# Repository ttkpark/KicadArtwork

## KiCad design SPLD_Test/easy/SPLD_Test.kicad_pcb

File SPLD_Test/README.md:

# CPLD-STM32 UI Controller & FND Multiplexer

## 📌 프로젝트 개요
본 프로젝트는 Altera MAX 3000A(EPM3064) CPLD를 활용하여 메인 MCU(STM32F030)의 부하를 줄이기 위한 하드웨어 UI 컨트롤러를 구현한 설계입니다.  
버튼 입력의 디바운싱(Debouncing), 0~31 양방향 카운터, 그리고 4-Digit 7-Segment(FND)의 다이나믹 구동(Multiplexing)을 CPLD 하드웨어 로직으로 분리 처리합니다.

## 🛠️ 개발 환경 및 하드웨어 사양
- **Target Device:** Altera MAX 3000A 계열 (`EPM3064ALC44-10`)
- **Main MCU:** STM32F030
- **IDE:** Quartus II 13.0 SP1 Web Edition
- **Clock Source:** STM32에서 공급하는 8kHz 외부 클럭 (`IO33`)

## 🎯 주요 기능 (Core Features)
1. **하드웨어 디바운싱 (Debouncing)**  
   - 8kHz 클럭 기반으로 약 18.7ms 딜레이 필터 구현  
   - 버튼 채터링을 소프트웨어 개입 없이 하드웨어에서 차단

2. **5-bit 양방향 카운터 (0~31)**  
   - `BTN1` 입력 시 -1 감소 (0에서 31 순환)  
   - `BTN2`, `BTN4` 입력 시 +1 증가 (31에서 0 순환)

3. **경량화된 BCD 변환 로직**  
   - EPM3064 매크로셀(64) 한계를 고려해 나눗셈/Double Dabble 대신  
   - `if-else` 기반 최적화된 뺄셈 로직으로 10의 자리/1의 자리 분리

4. **FND 다이나믹 멀티플렉싱**  
   - 8kHz를 32분주하여 약 250Hz로 4자리 Common Anode 순차 구동

5. **실시간 MCU 상태 보고**  
   - 카운터 5비트 상태(0~31)를 전용 I/O 핀 5개로 STM32에 비동기 전달

## 🔌 핀맵 할당 (Pin Mapping)
| 기능 그룹 | 신호명 | CPLD 핀 번호 | 비고 |
| :--- | :--- | :--- | :--- |
| **Clock** | `clk_8khz` | 33 | STM32에서 공급받는 8kHz 클럭 |
| **Button Input** | `btn1` | 1 | -1 감소 (Active Low) |
|  | `btn2` | 2 | +1 증가 (Active Low) |
|  | `btn4` | 4 | +1 증가 (Active Low) |
| **MCU Output** | `mcu_28` ~ `mcu_37` | 28, 29, 31, 34, 37 | 카운터 5비트 상태 실시간 출력 |
| **FND Segment** | `seg_a` ~ `dp` | 5, 6, 8, 9, 11, 12, 14, 16 | 7-Segment 제어 (Active Low) |
| **FND Common** | `com1` ~ `com4` | 18, 19, 20, 21 | 자릿수 제어 (Active High) |

> ⚠️ **주의 (하드웨어 핀맵 제약사항)**  
> 3번 핀은 VCC와 물리적으로 결선되어 있어 버튼 입력으로 사용하지 않습니다.

## 🚨 트러블슈팅 및 개발 가이드 (Lessons Learned)
프로젝트 수정/업로드 시 아래 항목을 반드시 확인하세요.

### 1) 98% 프로그래밍 실패(Verification Failed)
- **원인:** Verify 단계에서 JTAG 핀(TDI, TMS 등)에 연결된 외부 소자(FND 등)가 노이즈를 유발
- **해결책:**
  - 프로그래밍 시 **FND 모듈을 일시적으로 탈거**한 상태에서 업로드
  - 임시 조치로 Programmer에서 `Verify` 체크 해제 후 다운로드

### 2) 미사용 핀 설정 (Unused Pins Configuration)
- **원인:** Quartus 기본값이 미사용 핀을 `As output driving ground`로 설정해 전원 충돌 가능
- **해결책:**
  - `Assignments -> Device -> Device and Pin Options -> Unused Pins`
  - 값을 **`As input tri-stated`** 로 변경 후 전체 컴파일

### 3) 디바이스 라이브러리 지원
- MAX 3000A는 최신 Quartus Prime에서 미지원
- **Quartus II 13.0 SP1 Web Edition** 사용
- Device Installer에서 `MAX 3000A` 디바이스 팩(`.qdz`) 추가 설치 필요

## 📁 저장소 구조(예시)
```text
SPLD_Test/
├─ CPLD/          # Quartus 프로젝트/소스
├─ firmware/      # STM32F030 펌웨어 (OLED 모니터)
└─ README.md      # 본 문서
```

## 🔗 관련 문서
- 펌웨어 배선/핀 설명: `firmware/docs/CONNECTIONS.md`
- 펌웨어 개발 문서: `firmware/docs/DEVELOPMENT.md`

## 🙌 회고
하드웨어 핀맵 충돌, JTAG 간섭, 매크로셀 용량 최적화를 모두 통과해 완성한 프로젝트입니다.  
임베디드 하드웨어/펌웨어 협업 개발의 실제 제약과 해법이 담긴 결과물로, 유지보수 시 본 README와 관련 문서를 함께 참고하는 것을 권장합니다.

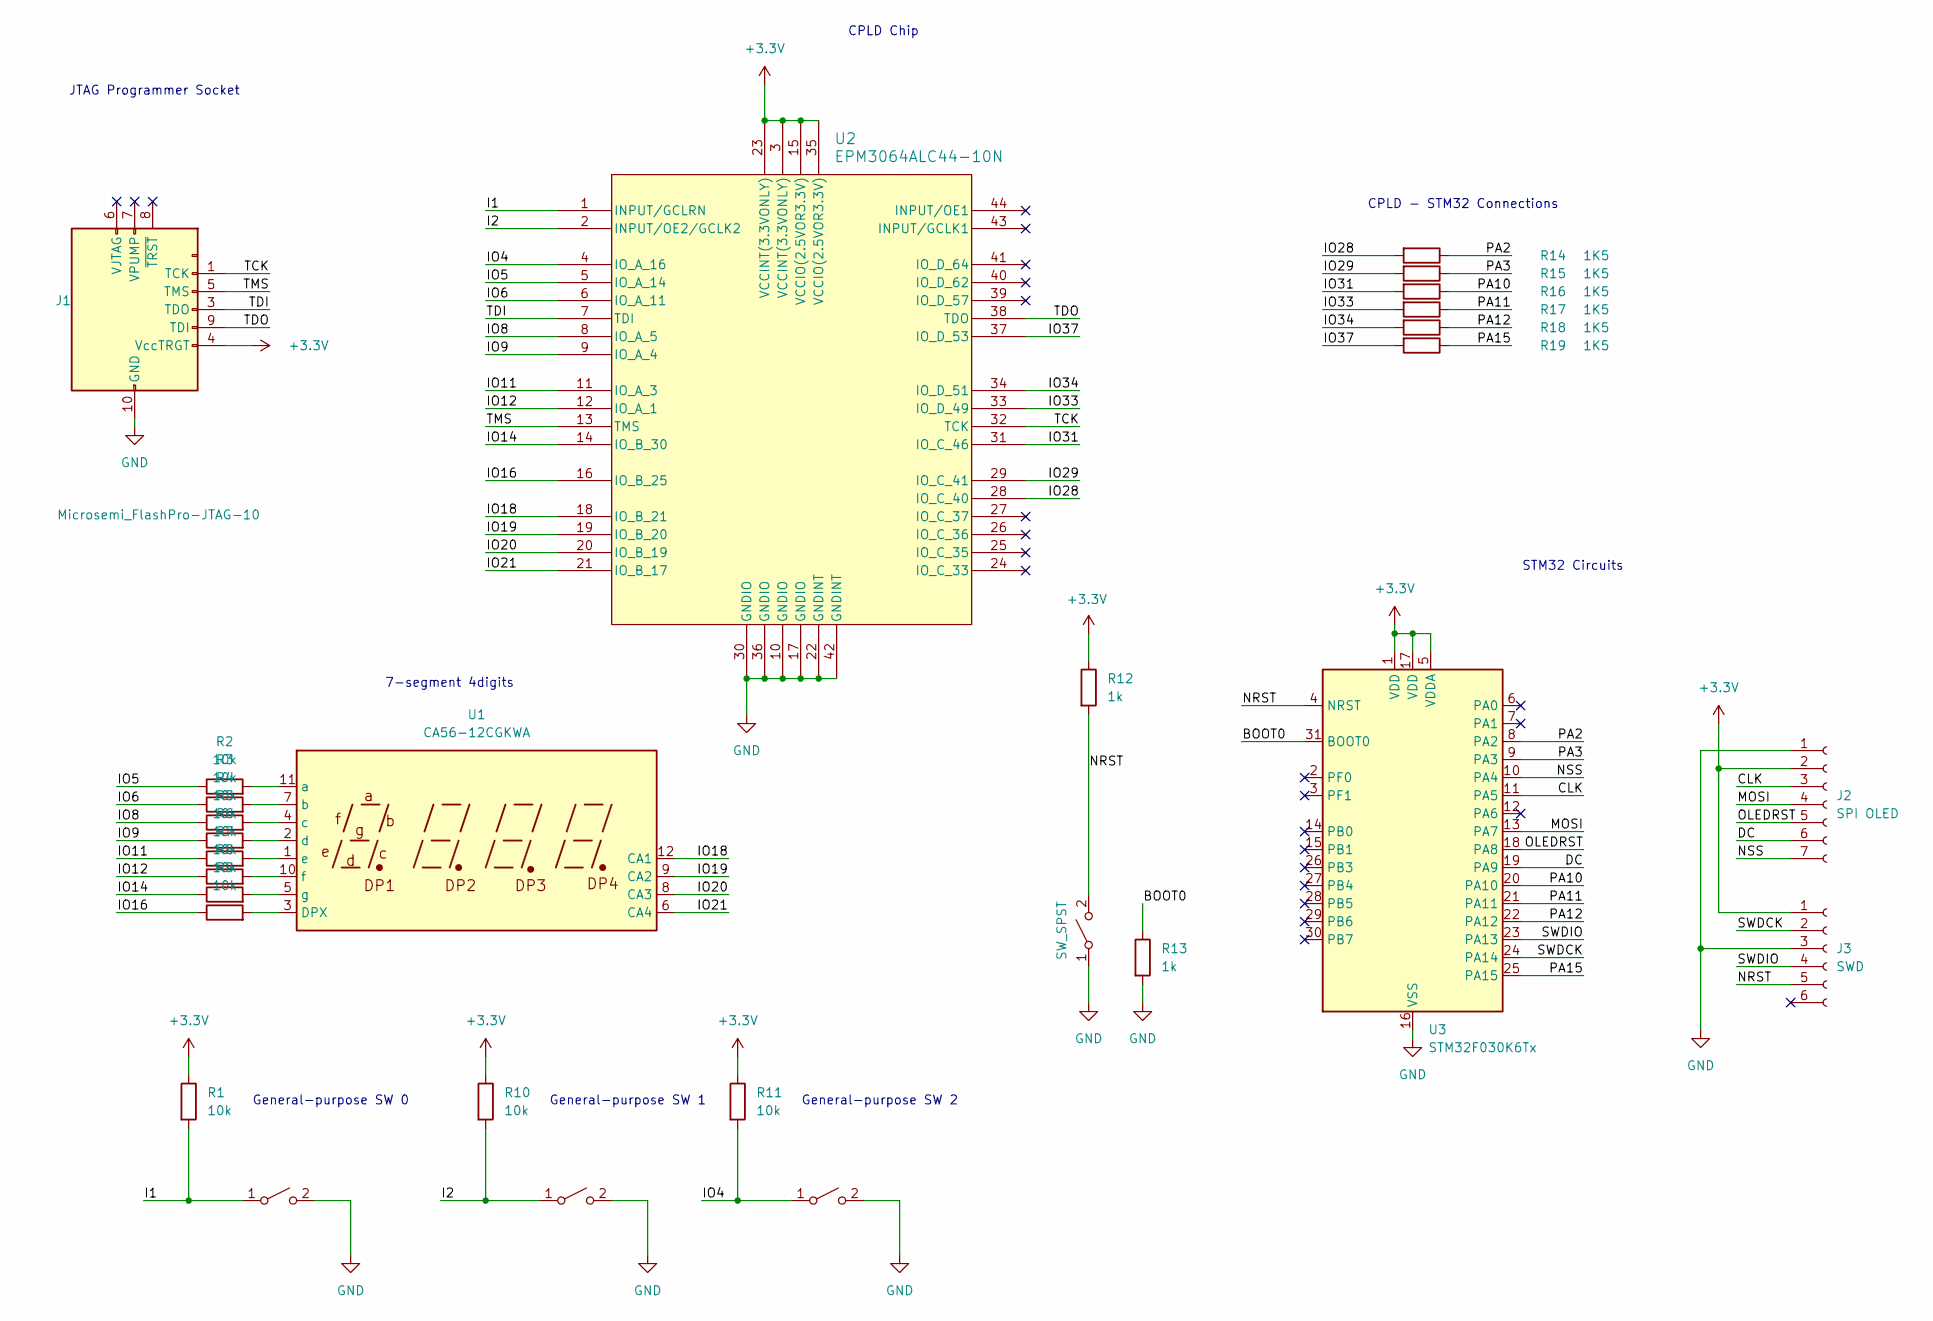
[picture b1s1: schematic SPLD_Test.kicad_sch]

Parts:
J1: Microsemi_FlashPro-JTAG-10; IDC-Header_2x05_P2.54mm_Vertical
J2: SPI OLED; PinSocket_1x07_P2.54mm_Vertical
J3: SWD; PinSocket_1x06_P2.54mm_Vertical
R1, R2, R3, R4, R5, R6, R7, R8, R9, R10, R11: 10k; R_0402_1005Metric_Pad0.72x0.64mm_HandSolder
R12, R13: 1k; R_0603_1608Metric_Pad0.98x0.95mm_HandSolder
R14, R15, R16, R17, R18, R19: 1K5; R_0603_1608Metric; LCSC C22843
SW1, SW2, SW3: SW_MEC_5E; SW_PUSH_6mm_H4.3mm
SW4: SW_SPST; SW_PUSH_6mm_H4.3mm
U1: CA56-12CGKWA
U2: EPM3064ALC44-10N; PLCC-44_THT-Socket
U3: STM32F030K6Tx; LQFP-32_7x7mm_P0.8mm

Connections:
+3.3V: J1.4 (VccTRGT), J2.2, J3.1, R1.1, R10.1, R11.1, R12.1, U2.3 (VCCINT(3.3VONLY)), U2.15 (VCCIO(2.5VOR3.3V)), U2.23 (VCCINT(3.3VONLY)), U2.35 (VCCIO(2.5VOR3.3V)), U3.1 (VDD), U3.5 (VDDA), U3.17 (VDD)
/BOOT0: R13.1, U3.31 (BOOT0)
/CLK: J2.3, U3.11 (PA5)
/DC: J2.6, U3.19 (PA9)
/I1: R1.2, SW1.1 (A), U2.1 (INPUT/GCLRN)
/I2: R10.2, SW2.1 (A), U2.2 (INPUT/OE2/GCLK2)
/IO4: R11.2, SW3.1 (A), U2.4 (IO_A_16)
/IO5: R2.1, U2.5 (IO_A_14)
/IO6: R3.1, U2.6 (IO_A_11)
/IO8: R4.1, U2.8 (IO_A_5)
/IO9: R5.1, U2.9 (IO_A_4)
/IO11: R6.1, U2.11 (IO_A_3)
/IO12: R7.1, U2.12 (IO_A_1)
/IO14: R8.1, U2.14 (IO_B_30)
/IO16: R9.1, U2.16 (IO_B_25)
/IO18: U1.12 (CA1), U2.18 (IO_B_21)
/IO19: U1.9 (CA2), U2.19 (IO_B_20)
/IO20: U1.8 (CA3), U2.20 (IO_B_19)
/IO21: U1.6 (CA4), U2.21 (IO_B_17)
/IO28: R14.2, U2.28 (IO_C_40)
/IO29: R15.2, U2.29 (IO_C_41)
/IO31: R16.2, U2.31 (IO_C_46)
/IO33: R17.2, U2.33 (IO_D_49)
/IO34: R18.2, U2.34 (IO_D_51)
/IO37: R19.2, U2.37 (IO_D_53)
/MOSI: J2.4, U3.13 (PA7)
/NRST: J3.5, R12.2, SW4.2 (B), U3.4 (NRST)
/NSS: J2.7, U3.10 (PA4)
/OLEDRST: J2.5, U3.18 (PA8)
/PA2: R14.1, U3.8 (PA2)
/PA3: R15.1, U3.9 (PA3)
/PA10: R16.1, U3.20 (PA10)
/PA11: R17.1, U3.21 (PA11)
/PA12: R18.1, U3.22 (PA12)
/PA15: R19.1, U3.25 (PA15)
/SWDCK: J3.2, U3.24 (PA14)
/SWDIO: J3.4, U3.23 (PA13)
/TCK: J1.1 (TCK), U2.32 (TCK)
/TDI: J1.3 (TDO), U2.7 (TDI)
/TDO: J1.9 (TDI), U2.38 (TDO)
/TMS: J1.5 (TMS), U2.13 (TMS)
GND: J1.2 (GND), J1.10 (GND), J2.1, J3.3, R13.2, SW1.2 (B), SW2.2 (B), SW3.2 (B), SW4.1 (A), U2.10 (GNDIO), U2.17 (GNDIO), U2.22 (GNDINT), U2.30 (GNDIO), U2.36 (GNDIO), U2.42 (GNDINT), U3.16 (VSS), U3.32 (VSS)
unnamed: R9.2, U1.3 (DPX)
unnamed: R2.2, U1.11 (a)
unnamed: R3.2, U1.7 (b)
unnamed: R4.2, U1.4 (c)
unnamed: R5.2, U1.2 (d)
unnamed: R6.2, U1.1 (e)
unnamed: R7.2, U1.10 (f)
unnamed: R8.2, U1.5 (g)

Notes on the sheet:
JTAG Programmer Socket
General-purpose SW 1
7-segment 4digits
STM32 Circuits
CPLD - STM32 Connections
CPLD Chip
General-purpose SW 2
General-purpose SW 0

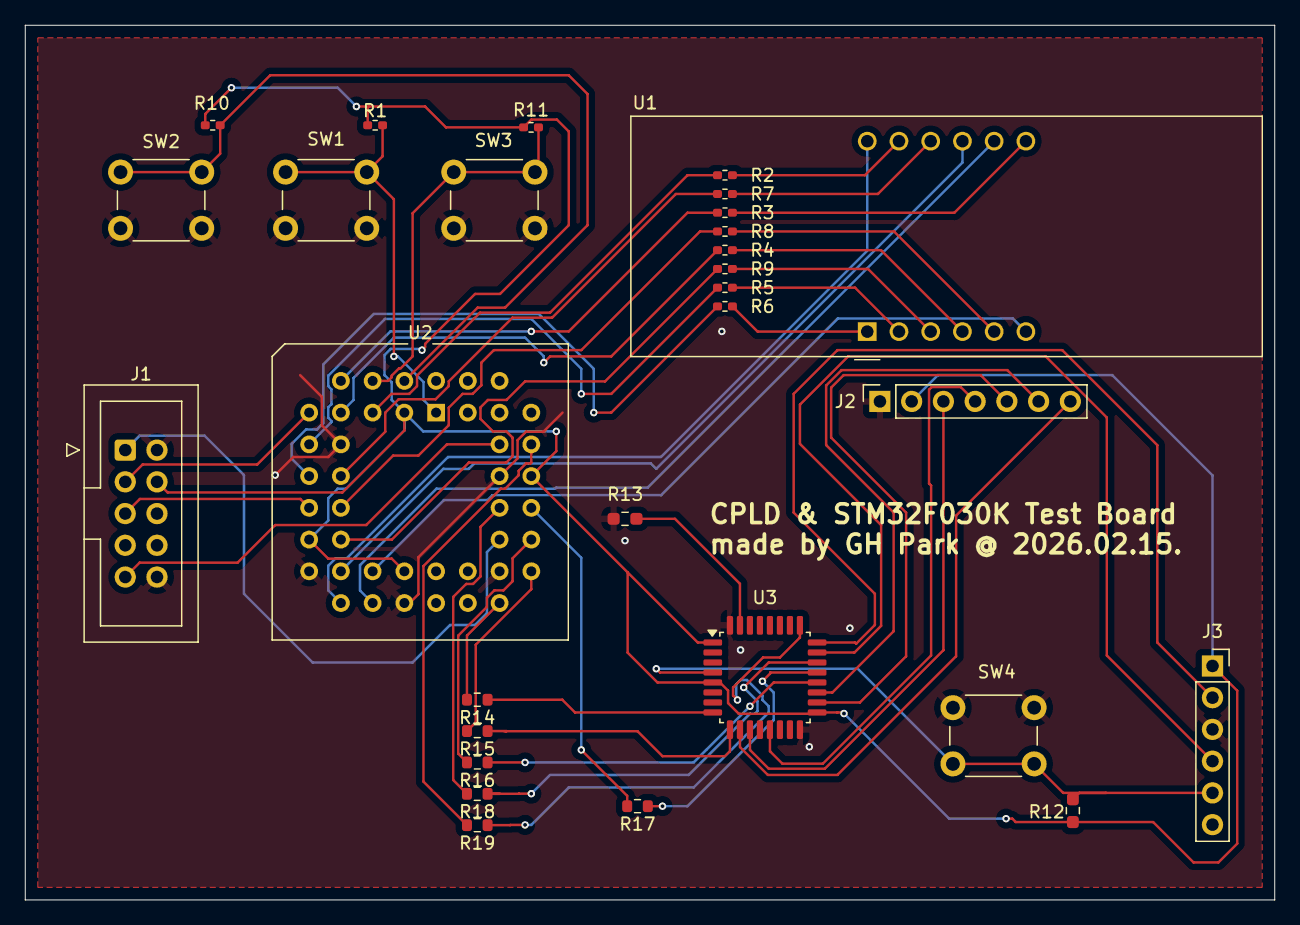
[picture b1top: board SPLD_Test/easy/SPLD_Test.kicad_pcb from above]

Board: 2 copper layers, 100.0 x 70.0 mm, 29 parts (0 on the bottom side), 50 nets.

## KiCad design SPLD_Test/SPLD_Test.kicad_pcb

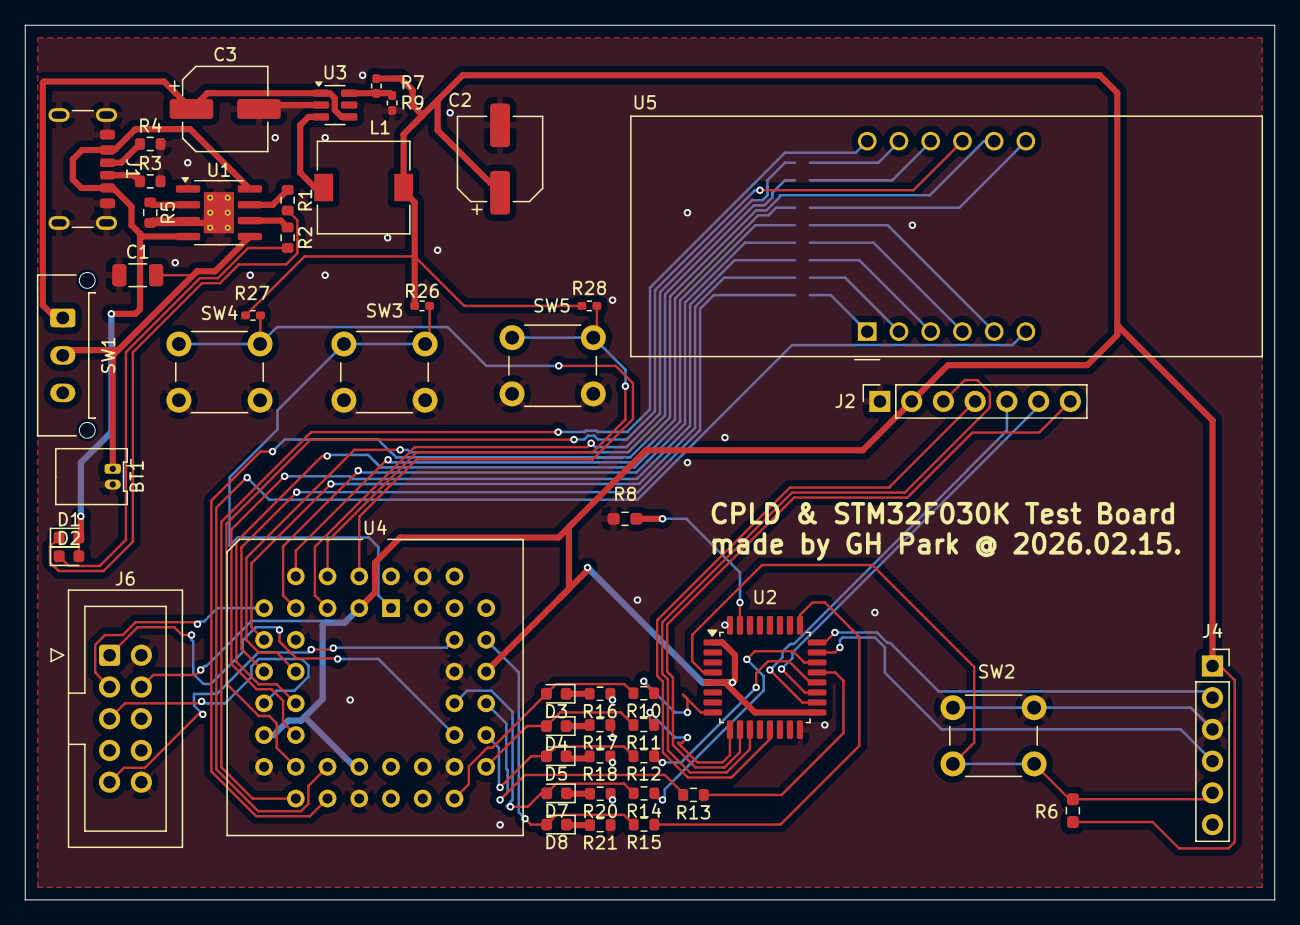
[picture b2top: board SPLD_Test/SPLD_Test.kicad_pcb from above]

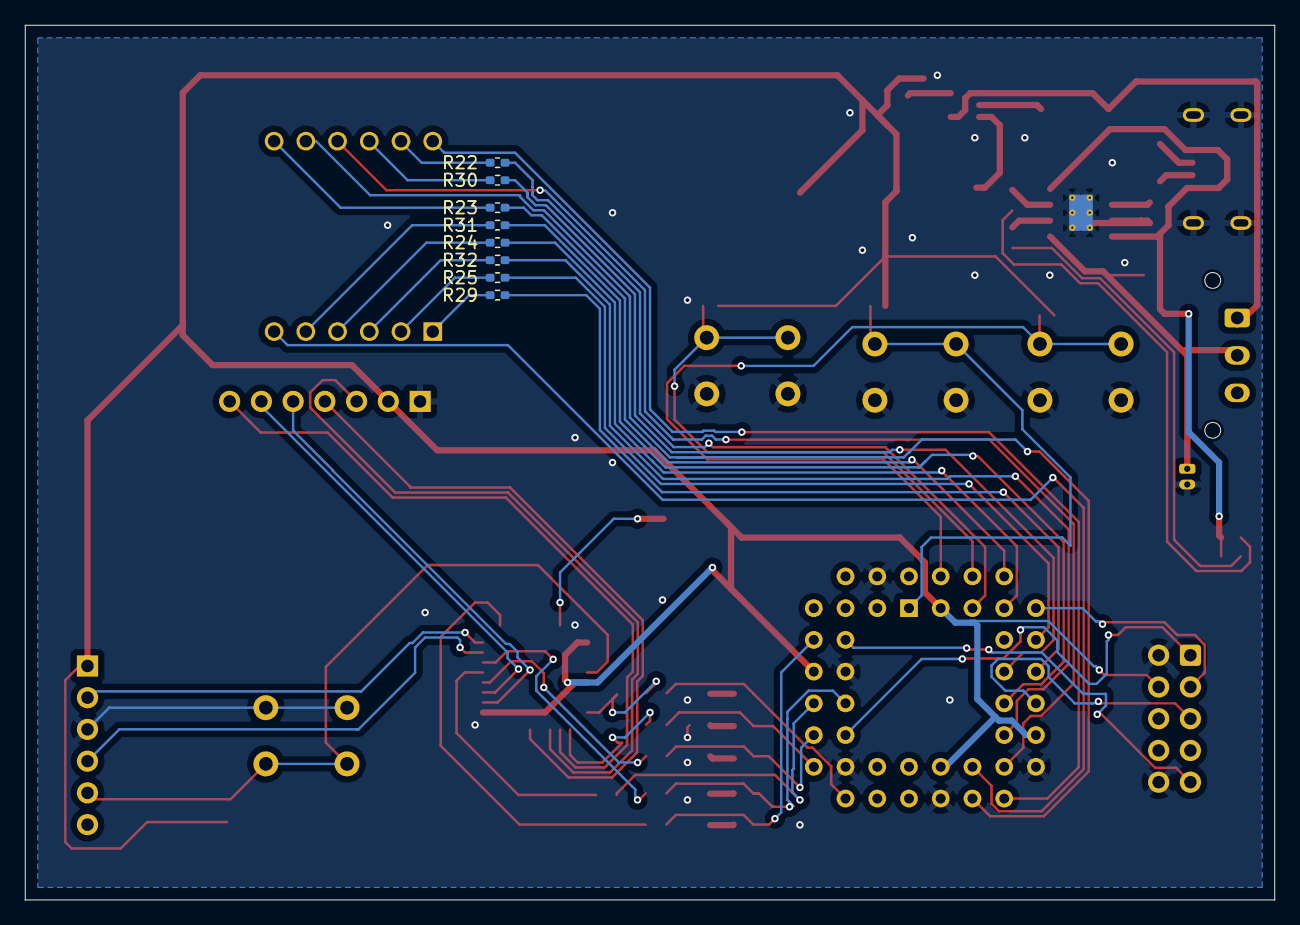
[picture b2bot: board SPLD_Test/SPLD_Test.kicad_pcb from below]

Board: 2 copper layers, 100.0 x 70.0 mm, 57 parts (8 on the bottom side), 67 nets.

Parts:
BT1: 3.7V; Molex_PicoBlade_53048-0210_1x02_P1.25mm_Horizontal
C1: 47u; C_1206_3216Metric
C2, C3: 47u; CP_Elec_6.3x5.7
D1: Charge; LED_0603_1608Metric
D2: Standby; LED_0603_1608Metric
D3, D4, D5, D7, D8: RED; LED_0603_1608Metric
J1: USB_C_Receptacle_PowerOnly_6P; USB_C_Receptacle_GCT_USB4125-xx-x-0190_6P_TopMnt_Horizontal
J2: SPI OLED 1.3in; PinSocket_1x07_P2.54mm_Vertical
J4: SWD; PinSocket_1x06_P2.54mm_Vertical
J6: Microsemi_FlashPro-JTAG-10; IDC-Header_2x05_P2.54mm_Vertical
L1: 10u; L_7.3x7.3_H3.5
R1, R2, R5, R10, R11, R12, R13, R14, R15, R16, R17, R18, R20, R21: 1K5; R_0603_1608Metric
R3, R4: 5K1; R_0603_1608Metric
R6, R8: 1k; R_0603_1608Metric_Pad0.98x0.95mm_HandSolder
R7: 2.35k; R_0402_1005Metric_Pad0.72x0.64mm_HandSolder
R9: 76.9R; R_0402_1005Metric_Pad0.72x0.64mm_HandSolder
R22, R23, R24, R25, R26, R27, R28, R29, R30, R31, R32: 10k; R_0402_1005Metric_Pad0.72x0.64mm_HandSolder
SW1: SW_SPDT; Molex_Micro-Fit_3.0_43650-0315_1x03_P3.00mm_Vertical
SW2, SW3, SW4, SW5: SW_MEC_5E; SW_PUSH_6mm_H4.3mm
U1: TP4056-42-ESOP8; SOIC-8-1EP_3.9x4.9mm_P1.27mm_EP2.41x3.3mm_ThermalVias
U2: STM32F030K6Tx; LQFP-32_7x7mm_P0.8mm
U3: EA8105; SOT-23-6
U4: EPM3064ALC44-10N; PLCC-44_THT-Socket
U5: CA56-12CGKWA

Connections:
+3.3V: C2.1, J2.2, J4.1, J6.4 (VccTRGT), L1.2, R6.1, R7.1, R26.1, R27.1, R28.1, U2.1 (VDD), U2.5 (VDDA), U2.17 (VDD), U4.3 (VCCINT(3.3VONLY)), U4.15 (VCCIO(2.5VOR3.3V)), U4.23 (VCCINT(3.3VONLY)), U4.35 (VCCIO(2.5VOR3.3V))
+5V: C3.1, SW1.1 (A), U3.1 (RUN), U3.4 (PWR)
/BOOT0: R8.1, U2.31 (BOOT0)
/CLK: J2.3, U2.11 (PA5)
/DC: J2.6, U2.19 (PA9)
/I1: R26.2, SW3.1 (A), U4.1 (INPUT/GCLRN)
/I2: R27.2, SW4.1 (A), U4.2 (INPUT/OE2/GCLK2)
/IO4: R28.2, SW5.1 (A), U4.4 (IO_A_16)
/IO5: R22.1, U4.5 (IO_A_14)
/IO6: R23.1, U4.6 (IO_A_11)
/IO8: R24.1, U4.8 (IO_A_5)
/IO9: R25.1, U4.9 (IO_A_4)
/IO11: R29.1, U4.11 (IO_A_3)
/IO12: R30.1, U4.12 (IO_A_1)
/IO14: R31.1, U4.14 (IO_B_30)
/IO16: R32.1, U4.16 (IO_B_25)
/IO18: U4.18 (IO_B_21), U5.12 (CA1)
/IO19: U4.19 (IO_B_20), U5.9 (CA2)
/IO20: U4.20 (IO_B_19), U5.8 (CA3)
/IO21: U4.21 (IO_B_17), U5.6 (CA4)
/IO28: D3.2 (A), R10.2, U4.28 (IO_C_40)
/IO29: D4.2 (A), R11.2, U4.29 (IO_C_41)
/IO31: D5.2 (A), R12.2, U4.31 (IO_C_46)
/IO33: R13.2, U4.33 (IO_D_49)
/IO34: D7.2 (A), R14.2, U4.34 (IO_D_51)
/IO37: D8.2 (A), R15.2, U4.37 (IO_D_53)
/MOSI: J2.4, U2.13 (PA7)
/NRST: J4.5, R6.2, SW2.2 (B), U2.4 (NRST)
/NSS: J2.7, U2.10 (PA4)
/OLEDRST: J2.5, U2.18 (PA8)
/PA2: R10.1, U2.8 (PA2)
/PA3: R11.1, U2.9 (PA3)
/PA10: R12.1, U2.20 (PA10)
/PA11: R13.1, U2.21 (PA11)
/PA12: R14.1, U2.22 (PA12)
/PA15: R15.1, U2.25 (PA15)
/SWDCK: J4.2, U2.24 (PA14)
/SWDIO: J4.4, U2.23 (PA13)
/TCK: J6.1 (TCK), U4.32 (TCK)
/TDI: J6.3 (TDO), U4.7 (TDI)
/TDO: J6.9 (TDI), U4.38 (TDO)
/TMS: J6.5 (TMS), U4.13 (TMS)
GND: BT1.2 (-), C1.1, C2.2, C3.2, J1.A12 (GND), J1.B12 (GND), J1.S1 (SHIELD), J2.1, J4.3, J6.2 (GND), J6.10 (GND), R3.2, R4.2, R5.2, R8.2, R9.2, R16.1, R17.1, R18.1, R20.1, R21.1, SW2.1 (A), SW3.2 (B), SW4.2 (B), SW5.2 (B), U1.1 (TEMP), U1.3 (GND), U1.9 (EPAD), U2.16 (VSS), U2.32 (VSS), U3.2 (GND), U4.10 (GNDIO), U4.17 (GNDIO), U4.22 (GNDINT), U4.30 (GNDIO), U4.36 (GNDIO), U4.42 (GNDINT)
unnamed: D1.1 (K), R1.2
unnamed: D2.1 (K), R2.2
unnamed: D3.1 (K), R16.2
unnamed: D4.1 (K), R17.2
unnamed: D5.1 (K), R18.2
unnamed: D7.1 (K), R20.2
unnamed: D8.1 (K), R21.2
unnamed: J1.A5 (CC1), R4.1
unnamed: J1.B5 (CC2), R3.1
unnamed: R5.1, U1.2 (PROG)
unnamed: R1.1, U1.7 (~CHRG)
unnamed: R2.1, U1.6 (~STDBY)
unnamed: R7.2, R9.1, U3.6 (FBK)
unnamed: L1.1, U3.3 (SW)
unnamed: R32.2, U5.3 (DPX)
unnamed: R22.2, U5.11 (a)
unnamed: R23.2, U5.7 (b)
unnamed: R24.2, U5.4 (c)
unnamed: R25.2, U5.2 (d)
unnamed: R29.2, U5.1 (e)
unnamed: R30.2, U5.10 (f)
unnamed: R31.2, U5.5 (g)
Vbat: BT1.1 (+), C1.2, SW1.2 (B), U1.5 (BAT)
Vusb: D1.2 (A), D2.2 (A), J1.A9 (VBUS), J1.B9 (VBUS), U1.4 (V_{CC}), U1.8 (CE)

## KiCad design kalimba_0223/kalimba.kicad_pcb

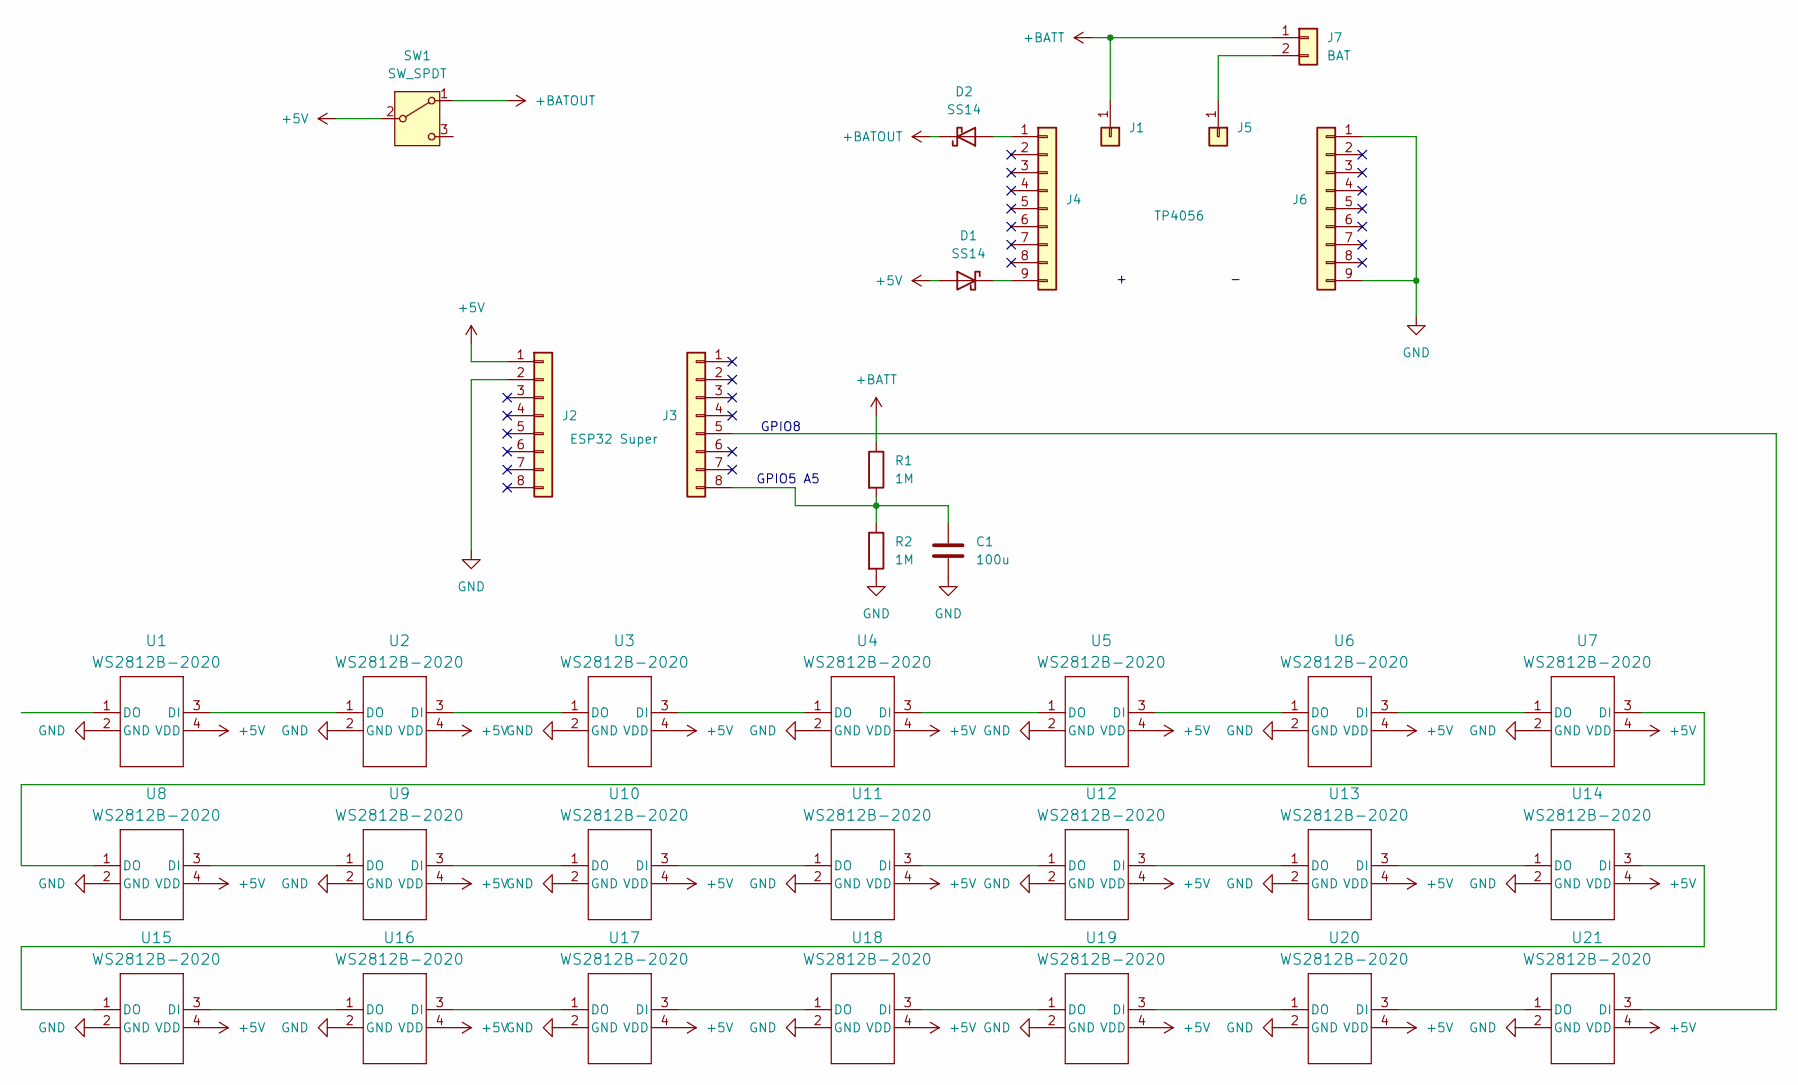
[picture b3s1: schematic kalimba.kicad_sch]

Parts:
C1: 100u; C_0402_1005Metric
D1, D2: SS14; D_SMA
J1, J5: Conn_01x01; PinHeader_1x01_P2.54mm_Vertical
J2: Conn_01x08; PinSocket_1x08_P2.54mm_Vertical
J3: ESP32 Super; PinSocket_1x08_P2.54mm_Vertical
J4: TP4056; PinSocket_1x09_P2.54mm_Vertical
J6: Conn_01x09; PinSocket_1x09_P2.54mm_Vertical
J7: BAT; PinHeader_1x02_P2.54mm_Vertical
R1, R2: 1M; R_0402_1005Metric
SW1: SW_SPDT; SK12D07VG4NSPA_CNK; LCSC C431547
U1, U2, U3, U4, U5, U6, U7, U8, U9, U10, U11, U12, U13, U14, U15, U16, U17, U18, U19, U20, U21: WS2812B-2020; SMT_12B-2020_WDS-L; LCSC C965555

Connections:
+5V: D1.2 (A), J2.1, SW1.2 (B), U1.4 (VDD), U2.4 (VDD), U3.4 (VDD), U4.4 (VDD), U5.4 (VDD), U6.4 (VDD), U7.4 (VDD), U8.4 (VDD), U9.4 (VDD), U10.4 (VDD), U11.4 (VDD), U12.4 (VDD), U13.4 (VDD), U14.4 (VDD), U15.4 (VDD), U16.4 (VDD), U17.4 (VDD), U18.4 (VDD), U19.4 (VDD), U20.4 (VDD), U21.4 (VDD)
+BATOUT: D2.1 (K), SW1.1 (A)
+BATT: J1.1, J7.1, R1.1
GND: C1.2, J2.2, J6.1, J6.9, R2.2, U1.2 (GND), U2.2 (GND), U3.2 (GND), U4.2 (GND), U5.2 (GND), U6.2 (GND), U7.2 (GND), U8.2 (GND), U9.2 (GND), U10.2 (GND), U11.2 (GND), U12.2 (GND), U13.2 (GND), U14.2 (GND), U15.2 (GND), U16.2 (GND), U17.2 (GND), U18.2 (GND), U19.2 (GND), U20.2 (GND), U21.2 (GND)
unnamed: D1.1 (K), J4.9
unnamed: D2.2 (A), J4.1
unnamed: J3.5, U21.3 (DI)
unnamed: C1.1, J3.8, R1.2, R2.1
unnamed: J5.1, J7.2
unnamed: U1.3 (DI), U2.1 (DO)
unnamed: U2.3 (DI), U3.1 (DO)
unnamed: U3.3 (DI), U4.1 (DO)
unnamed: U4.3 (DI), U5.1 (DO)
unnamed: U5.3 (DI), U6.1 (DO)
unnamed: U6.3 (DI), U7.1 (DO)
unnamed: U7.3 (DI), U8.1 (DO)
unnamed: U8.3 (DI), U9.1 (DO)
unnamed: U10.3 (DI), U11.1 (DO)
unnamed: U9.3 (DI), U10.1 (DO)
unnamed: U11.3 (DI), U12.1 (DO)
unnamed: U12.3 (DI), U13.1 (DO)
unnamed: U13.3 (DI), U14.1 (DO)
unnamed: U14.3 (DI), U15.1 (DO)
unnamed: U15.3 (DI), U16.1 (DO)
unnamed: U16.3 (DI), U17.1 (DO)
unnamed: U17.3 (DI), U18.1 (DO)
unnamed: U18.3 (DI), U19.1 (DO)
unnamed: U19.3 (DI), U20.1 (DO)
unnamed: U20.3 (DI), U21.1 (DO)

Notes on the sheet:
GPIO8
+ -
GPIO5 A5

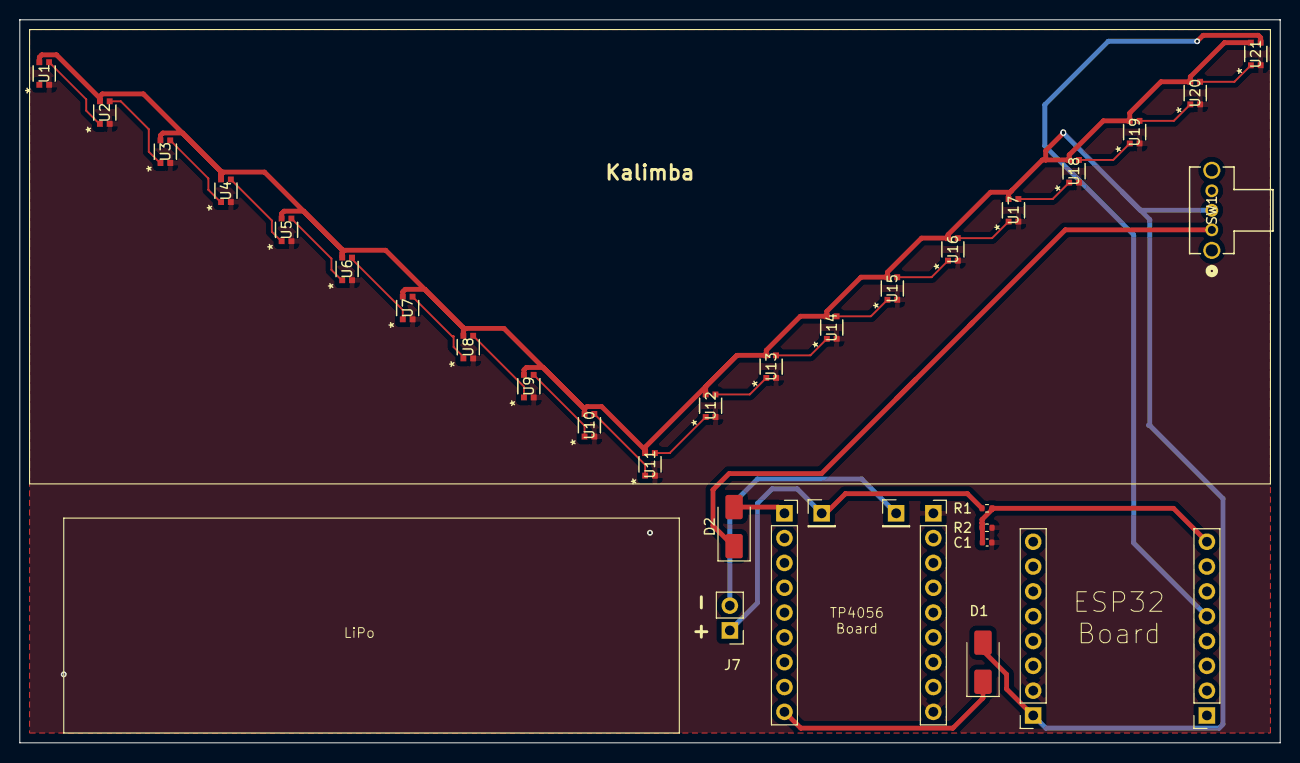
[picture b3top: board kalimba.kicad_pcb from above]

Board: 2 copper layers, 129.0 x 74.0 mm, 34 parts (0 on the bottom side), 29 nets.

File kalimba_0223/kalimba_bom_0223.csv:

Designator	Comment	Footprint	LCSC
SW1	SW_SPDT	SK12D07VG4NSPA_CNK	C431547
"R1,R2"	1M	Resistor_SMD:R_0402_1005Metric	
"U1,U2,U3,U4,U5,U6,U7,U8,U9,U10,U11,U12,U13,U14,U15,U16,U17,U18,U19,U20,U21"	WS2812B-2020	GHLED:SMT_12B-2020_WDS-L	C965555
D1	SS14	Diode_SMD:D_SMA	
J6	Conn_01x09	Connector_PinSocket_2.54mm:PinSocket_1x09_P2.54mm_Vertical	
J4	TP4056	Connector_PinSocket_2.54mm:PinSocket_1x09_P2.54mm_Vertical	
J3	ESP32 Super	Connector_PinSocket_2.54mm:PinSocket_1x08_P2.54mm_Vertical	
J2	Conn_01x08	Connector_PinSocket_2.54mm:PinSocket_1x08_P2.54mm_Vertical	
J7	BAT	Connector_PinHeader_2.54mm:PinHeader_1x02_P2.54mm_Vertical	
"J1,J5"	Conn_01x01	Connector_PinHeader_2.54mm:PinHeader_1x01_P2.54mm_Vertical	
C1	100u	Capacitor_SMD:C_0402_1005Metric

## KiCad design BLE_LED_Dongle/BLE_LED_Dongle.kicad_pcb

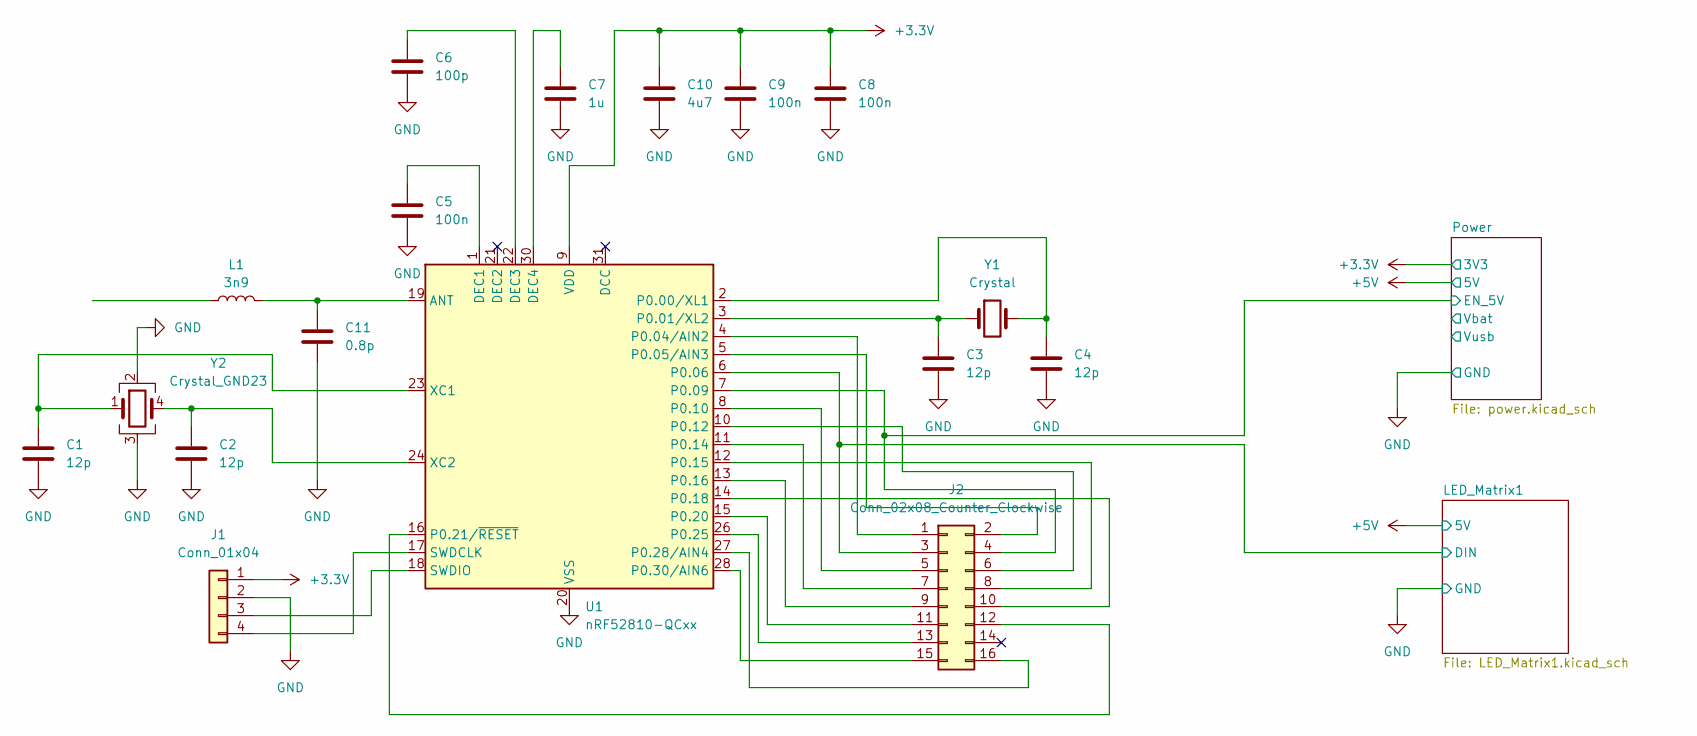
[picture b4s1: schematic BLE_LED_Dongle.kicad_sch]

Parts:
C1, C2, C3, C4: 12p; C_0402_1005Metric; LCSC C76948
C5, C8, C9: 100n; C_0402_1005Metric; LCSC C1525
C6: 100p; C_0402_1005Metric; LCSC C26409
C7: 1u; C_0402_1005Metric; LCSC C14445
C10: 4u7; C_0402_1005Metric; LCSC C23733
C11: 0.8p; C_0402_1005Metric; LCSC C327032
J1: Conn_01x04; PinHeader_1x04_P2.54mm_Horizontal; LCSC C492412
J2: Conn_02x08_Counter_Clockwise; PinHeader_2x08_P2.54mm_Vertical
L1: 3n9; L_0402_1005Metric; LCSC C98062
U1: nRF52810-QCxx; QFN-32-1EP_5x5mm_P0.5mm_EP3.6x3.6mm; LCSC C519278
Y1: Crystal; Crystal_SMD_3215-2Pin_3.2x1.5mm; LCSC C97606
Y2: Crystal_GND23; Crystal_SMD_2016-4Pin_2.0x1.6mm; LCSC C2965582

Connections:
+3.3V: C8.1, C9.1, C10.1, J1.1, U1.9 (VDD), U1.25 (VDD), U1.32 (VDD); also elsewhere on the board
/LED_Matrix1/DIN: J2.3 (Pin_2), U1.6 (P0.06); also elsewhere on the board
/Power/EN_5V: J2.4 (Pin_15), U1.7 (P0.09); also elsewhere on the board
GND: C1.2, C2.2, C3.2, C4.2, C5.2, C6.2, C7.2, C8.2, C9.2, C10.2, C11.2, J1.2, U1.20 (VSS), U1.29 (VSS), U1.33 (VSS), Y2.2, Y2.3; also elsewhere on the board
unnamed: J1.3, U1.18 (SWDIO)
unnamed: J1.4, U1.17 (SWDCLK)
unnamed: J2.1, U1.4 (P0.04/AIN2)
unnamed: J2.5 (Pin_3), U1.8 (P0.10)
unnamed: J2.7 (Pin_4), U1.11 (P0.14)
unnamed: J2.9 (Pin_5), U1.13 (P0.16)
unnamed: J2.11 (Pin_6), U1.15 (P0.20)
unnamed: J2.13 (Pin_7), U1.26 (P0.25)
unnamed: J2.15 (Pin_8), U1.28 (P0.30/AIN6)
unnamed: J2.12 (Pin_11), U1.16 (P0.21/~RESET)
unnamed: J2.10 (Pin_12), U1.14 (P0.18)
unnamed: J2.8 (Pin_13), U1.12 (P0.15)
unnamed: J2.6 (Pin_14), U1.10 (P0.12)
unnamed: J2.2 (Pin_16), U1.5 (P0.05/AIN3)
unnamed: C11.1, L1.2, U1.19 (ANT)
unnamed: C5.1, U1.1 (DEC1)
unnamed: C6.1, U1.22 (DEC3)
unnamed: C7.1, U1.30 (DEC4)
unnamed: C4.1, U1.2 (P0.00/XL1), Y1.2
unnamed: C3.1, U1.3 (P0.01/XL2), Y1.1
unnamed: J2.16, U1.27 (P0.28/AIN4)
unnamed: C1.1, U1.23 (XC1), Y2.1
unnamed: C2.1, U1.24 (XC2), Y2.4

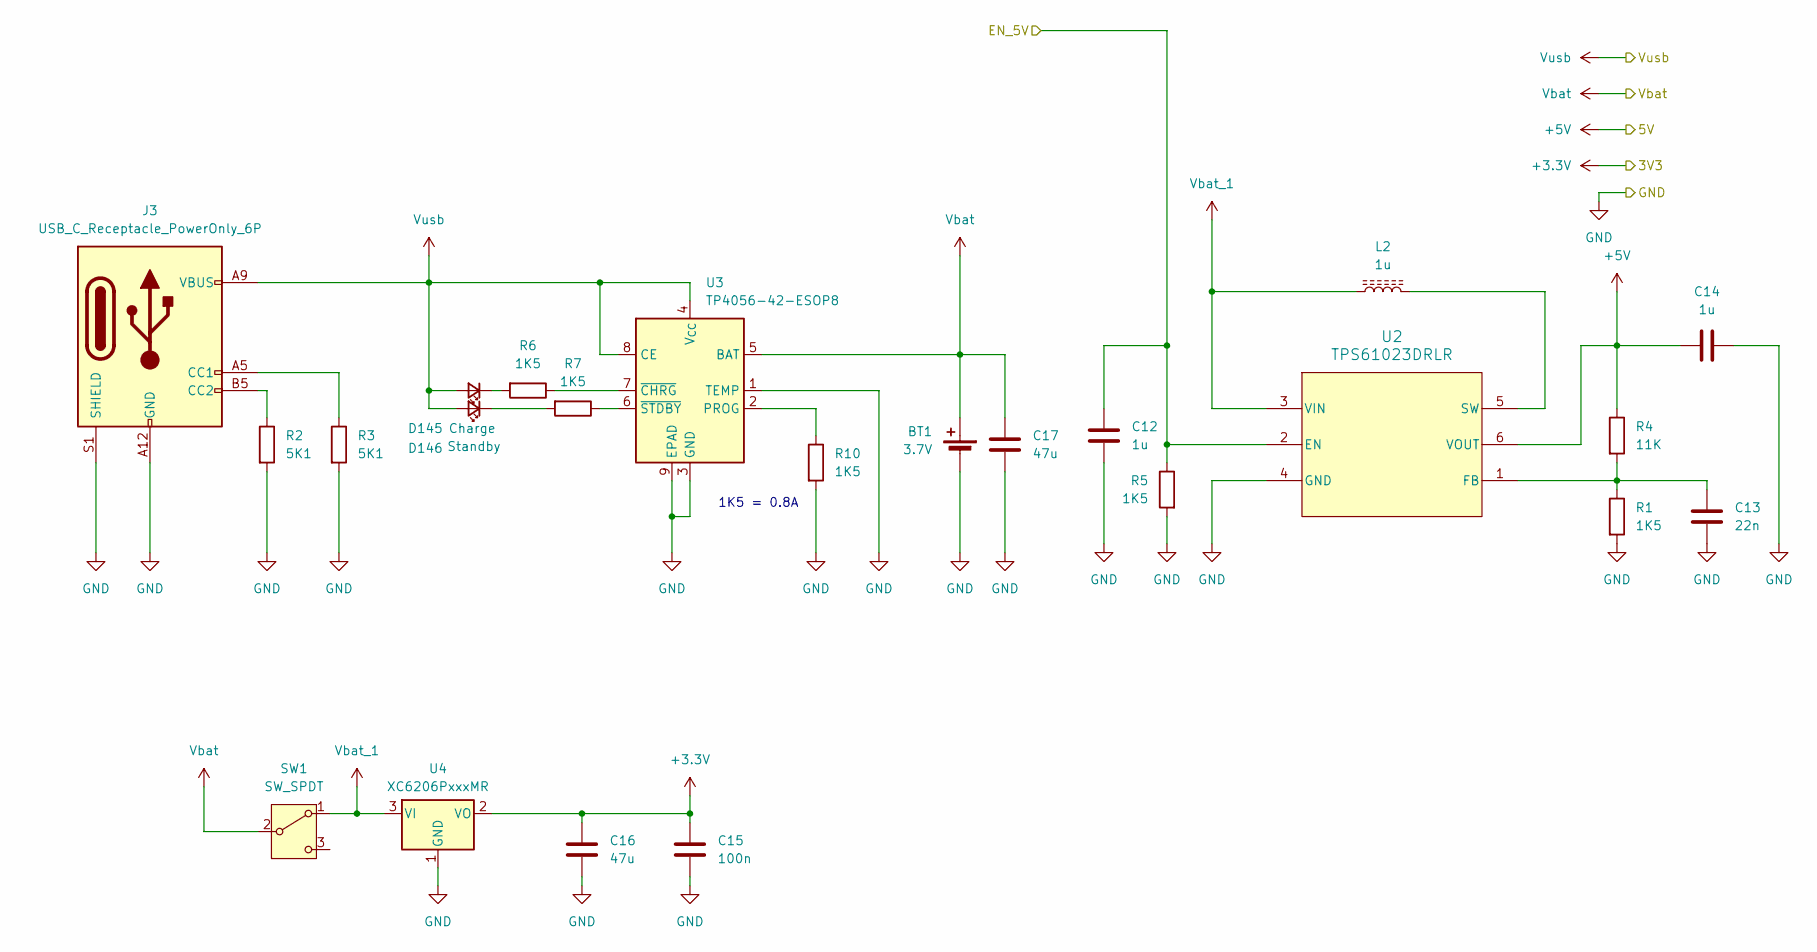
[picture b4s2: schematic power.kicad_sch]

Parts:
BT1: 3.7V; JST_PH_S2B-PH-K_1x02_P2.00mm_Horizontal; LCSC C295747
C12, C14: 1u; C_0402_1005Metric; LCSC C14445
C13: 22n; C_0402_1005Metric; LCSC C337699
C15: 100n; C_0402_1005Metric; LCSC C1525
C16, C17: 47u; C_1206_3216Metric; LCSC C68361
D145: Charge; LED_0603_1608Metric; LCSC C19171390
D146: Standby; LED_0603_1608Metric; LCSC C22371297
J3: USB_C_Receptacle_PowerOnly_6P; USB_C_Receptacle_GCT_USB4125-xx-x-0190_6P_TopMnt_Horizontal; LCSC C668623
L2: 1u; L_6.3x6.3_H3; LCSC C5343973
R1, R5, R6, R7, R10: 1K5; R_0603_1608Metric; LCSC C22843
R2, R3: 5K1; R_0603_1608Metric; LCSC C23186
R4: 11K; R_0603_1608Metric; LCSC C2906986
SW1: SW_SPDT; SK12D07VG4NSPA_CNK; LCSC C431547
U2: TPS61023DRLR; DRL0006A; LCSC C919459
U3: TP4056-42-ESOP8; SOIC-8-1EP_3.9x4.9mm_P1.27mm_EP2.41x3.3mm_ThermalVias; LCSC C382139
U4: XC6206PxxxMR; SOT-23-3; LCSC C5446

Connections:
+3.3V: C15.2, C16.2, U4.2 (VO); also elsewhere on the board
+5V: C14.1, R4.1, U2.6 (VOUT); also elsewhere on the board
/Power/EN_5V: C12.1, R5.1, U2.2 (EN); also elsewhere on the board
GND: BT1.2 (-), C12.2, C13.2, C14.2, C15.1, C16.1, C17.1, J3.A12 (GND), J3.B12 (GND), J3.S1 (SHIELD), R1.2, R2.2, R3.2, R5.2, R10.2, U2.4 (GND), U3.1 (TEMP), U3.3 (GND), U3.9 (EPAD), U4.1 (GND); also elsewhere on the board
unnamed: D145.1 (K), R6.2
unnamed: D146.1 (K), R7.2
unnamed: J3.A5 (CC1), R3.1
unnamed: J3.B5 (CC2), R2.1
unnamed: C13.1, R1.1, R4.2, U2.1 (FB)
unnamed: L2.2, U2.5 (SW)
unnamed: R10.1, U3.2 (PROG)
unnamed: R6.1, U3.7 (~CHRG)
unnamed: R7.1, U3.6 (~STDBY)
Vbat: BT1.1 (+), C17.2, SW1.2 (B), U3.5 (BAT)
Vbat_1: L2.1, SW1.1 (A), U2.3 (VIN), U4.3 (VI)
Vusb: D145.2 (A), D146.2 (A), J3.A9 (VBUS), J3.B9 (VBUS), U3.4 (V_{CC}), U3.8 (CE)

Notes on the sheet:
1K5 = 0.8A
